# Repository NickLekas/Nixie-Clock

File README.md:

v1 is broken and required some bodge wires to work. I have not updated the schematic and PCB to correct my mistakes. It also has some deficencies in the dimming circuit resulint in a quiet, but audible whine.

v2 is in progress and will fix many issues and make the clock easier to update. It wil be using an RP2040.

Features
- Automatic time seting using GPS
- User sets their time zone using dip switches
- Tubes dim with ambient light
- Day light savings time will be controlled using a +/-1 switch 
- Plenty of test points for testing and hacking
- USB C for power and data

The goal of this is to be a program once project so the end user will never need to plug it into a computer. But if they do, the RP2040 will make firmware updates easy

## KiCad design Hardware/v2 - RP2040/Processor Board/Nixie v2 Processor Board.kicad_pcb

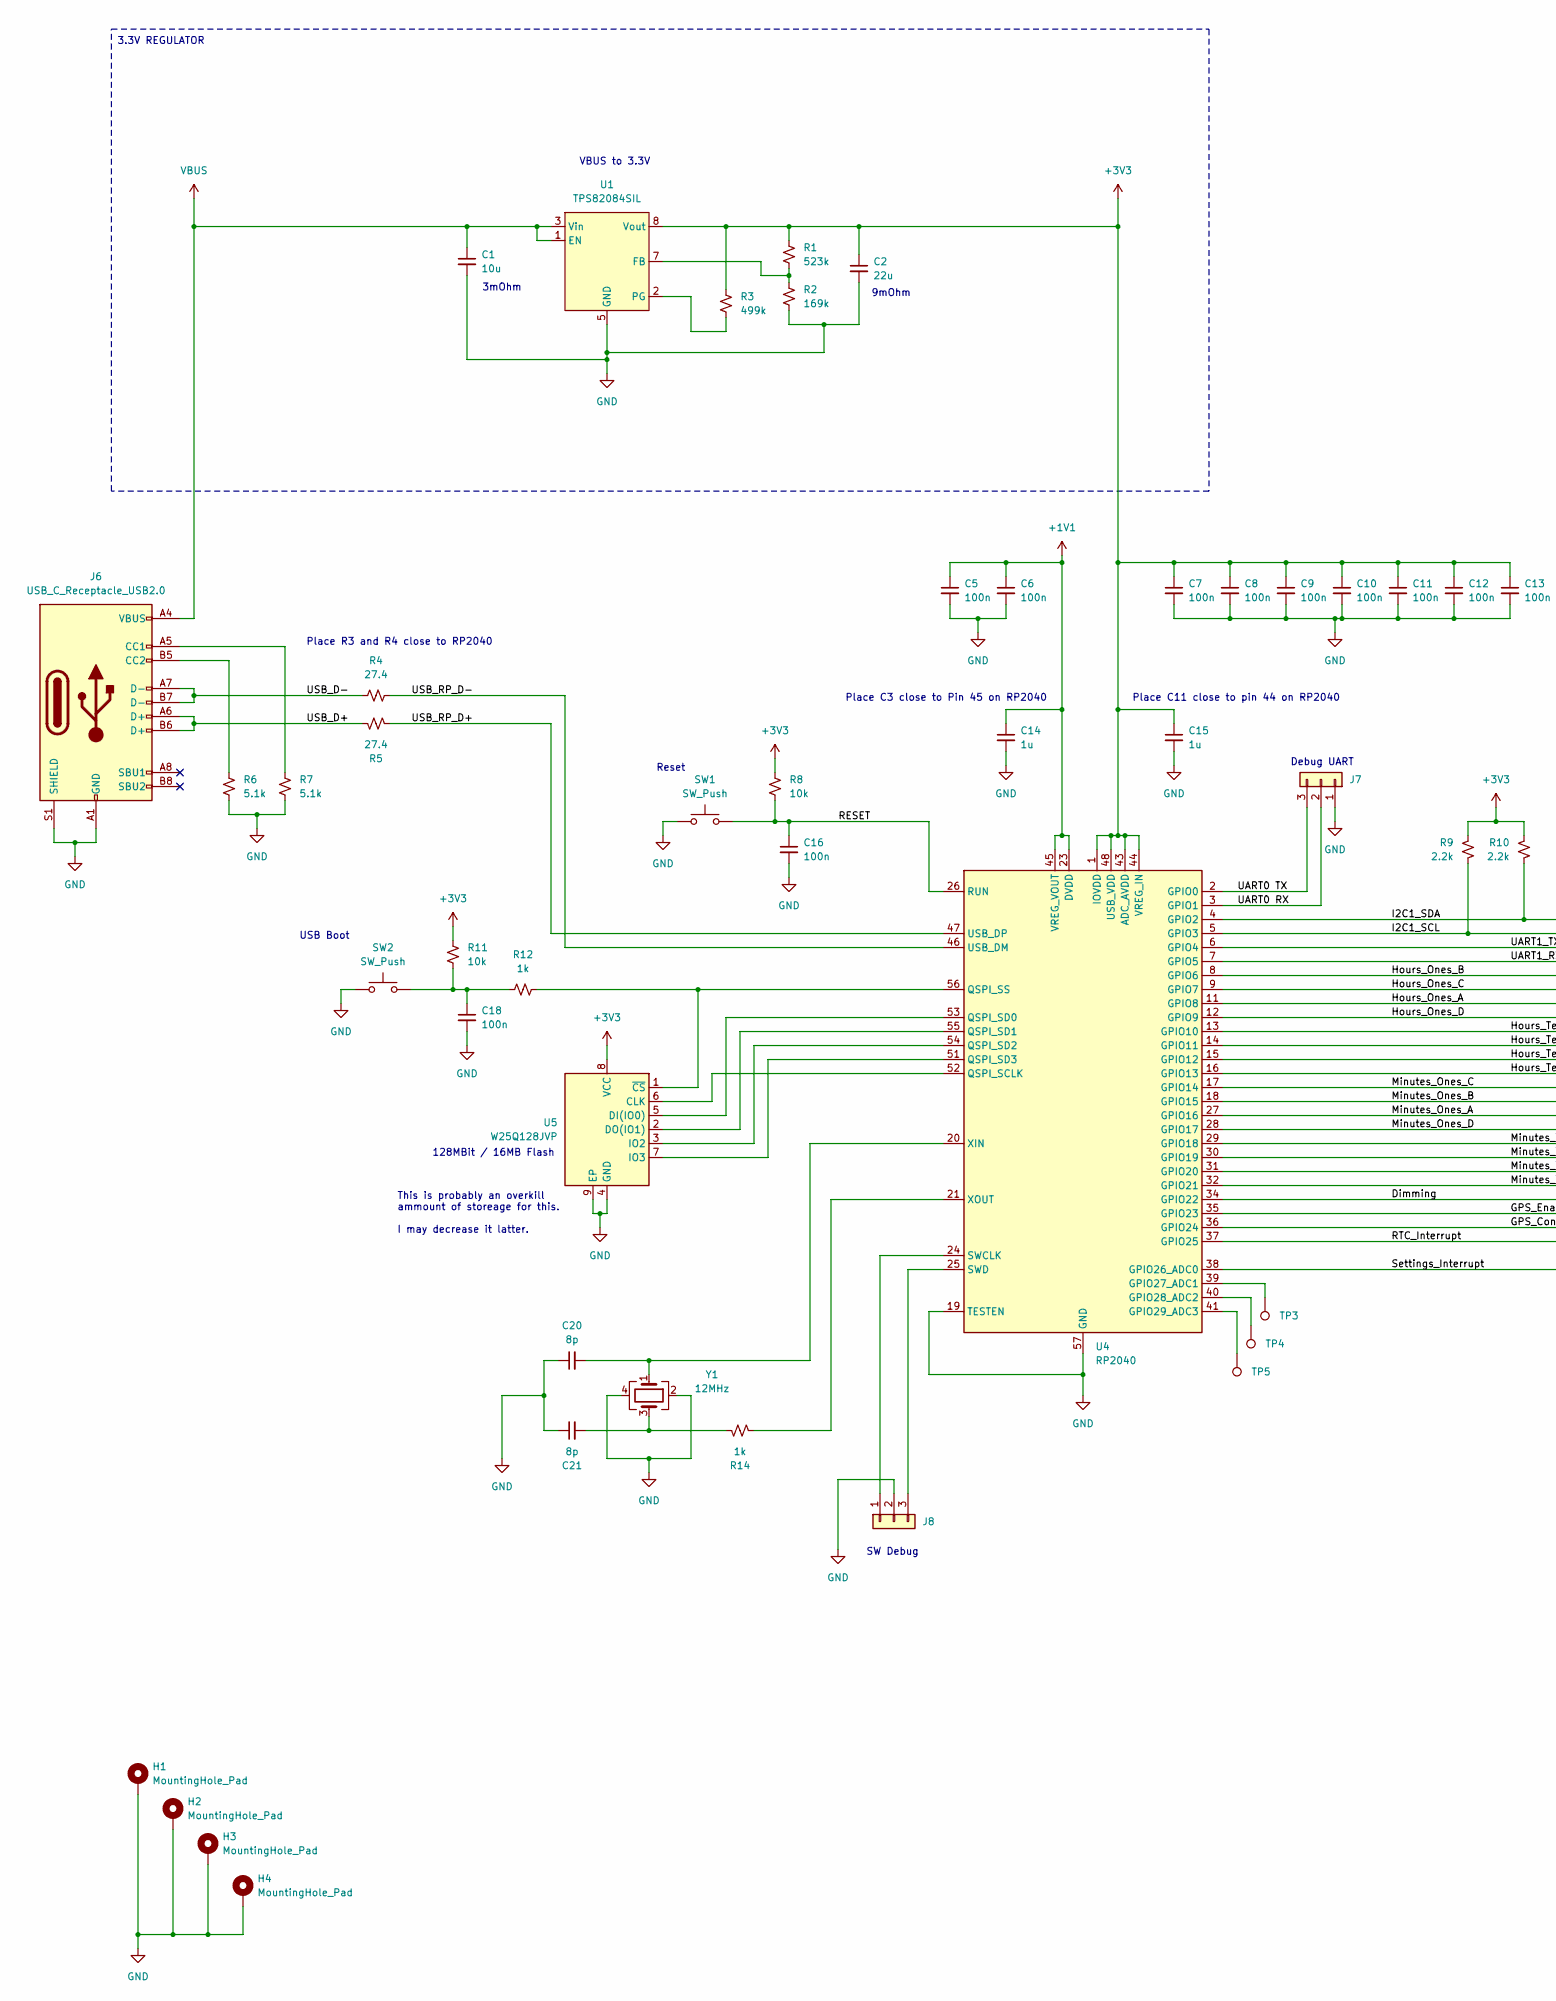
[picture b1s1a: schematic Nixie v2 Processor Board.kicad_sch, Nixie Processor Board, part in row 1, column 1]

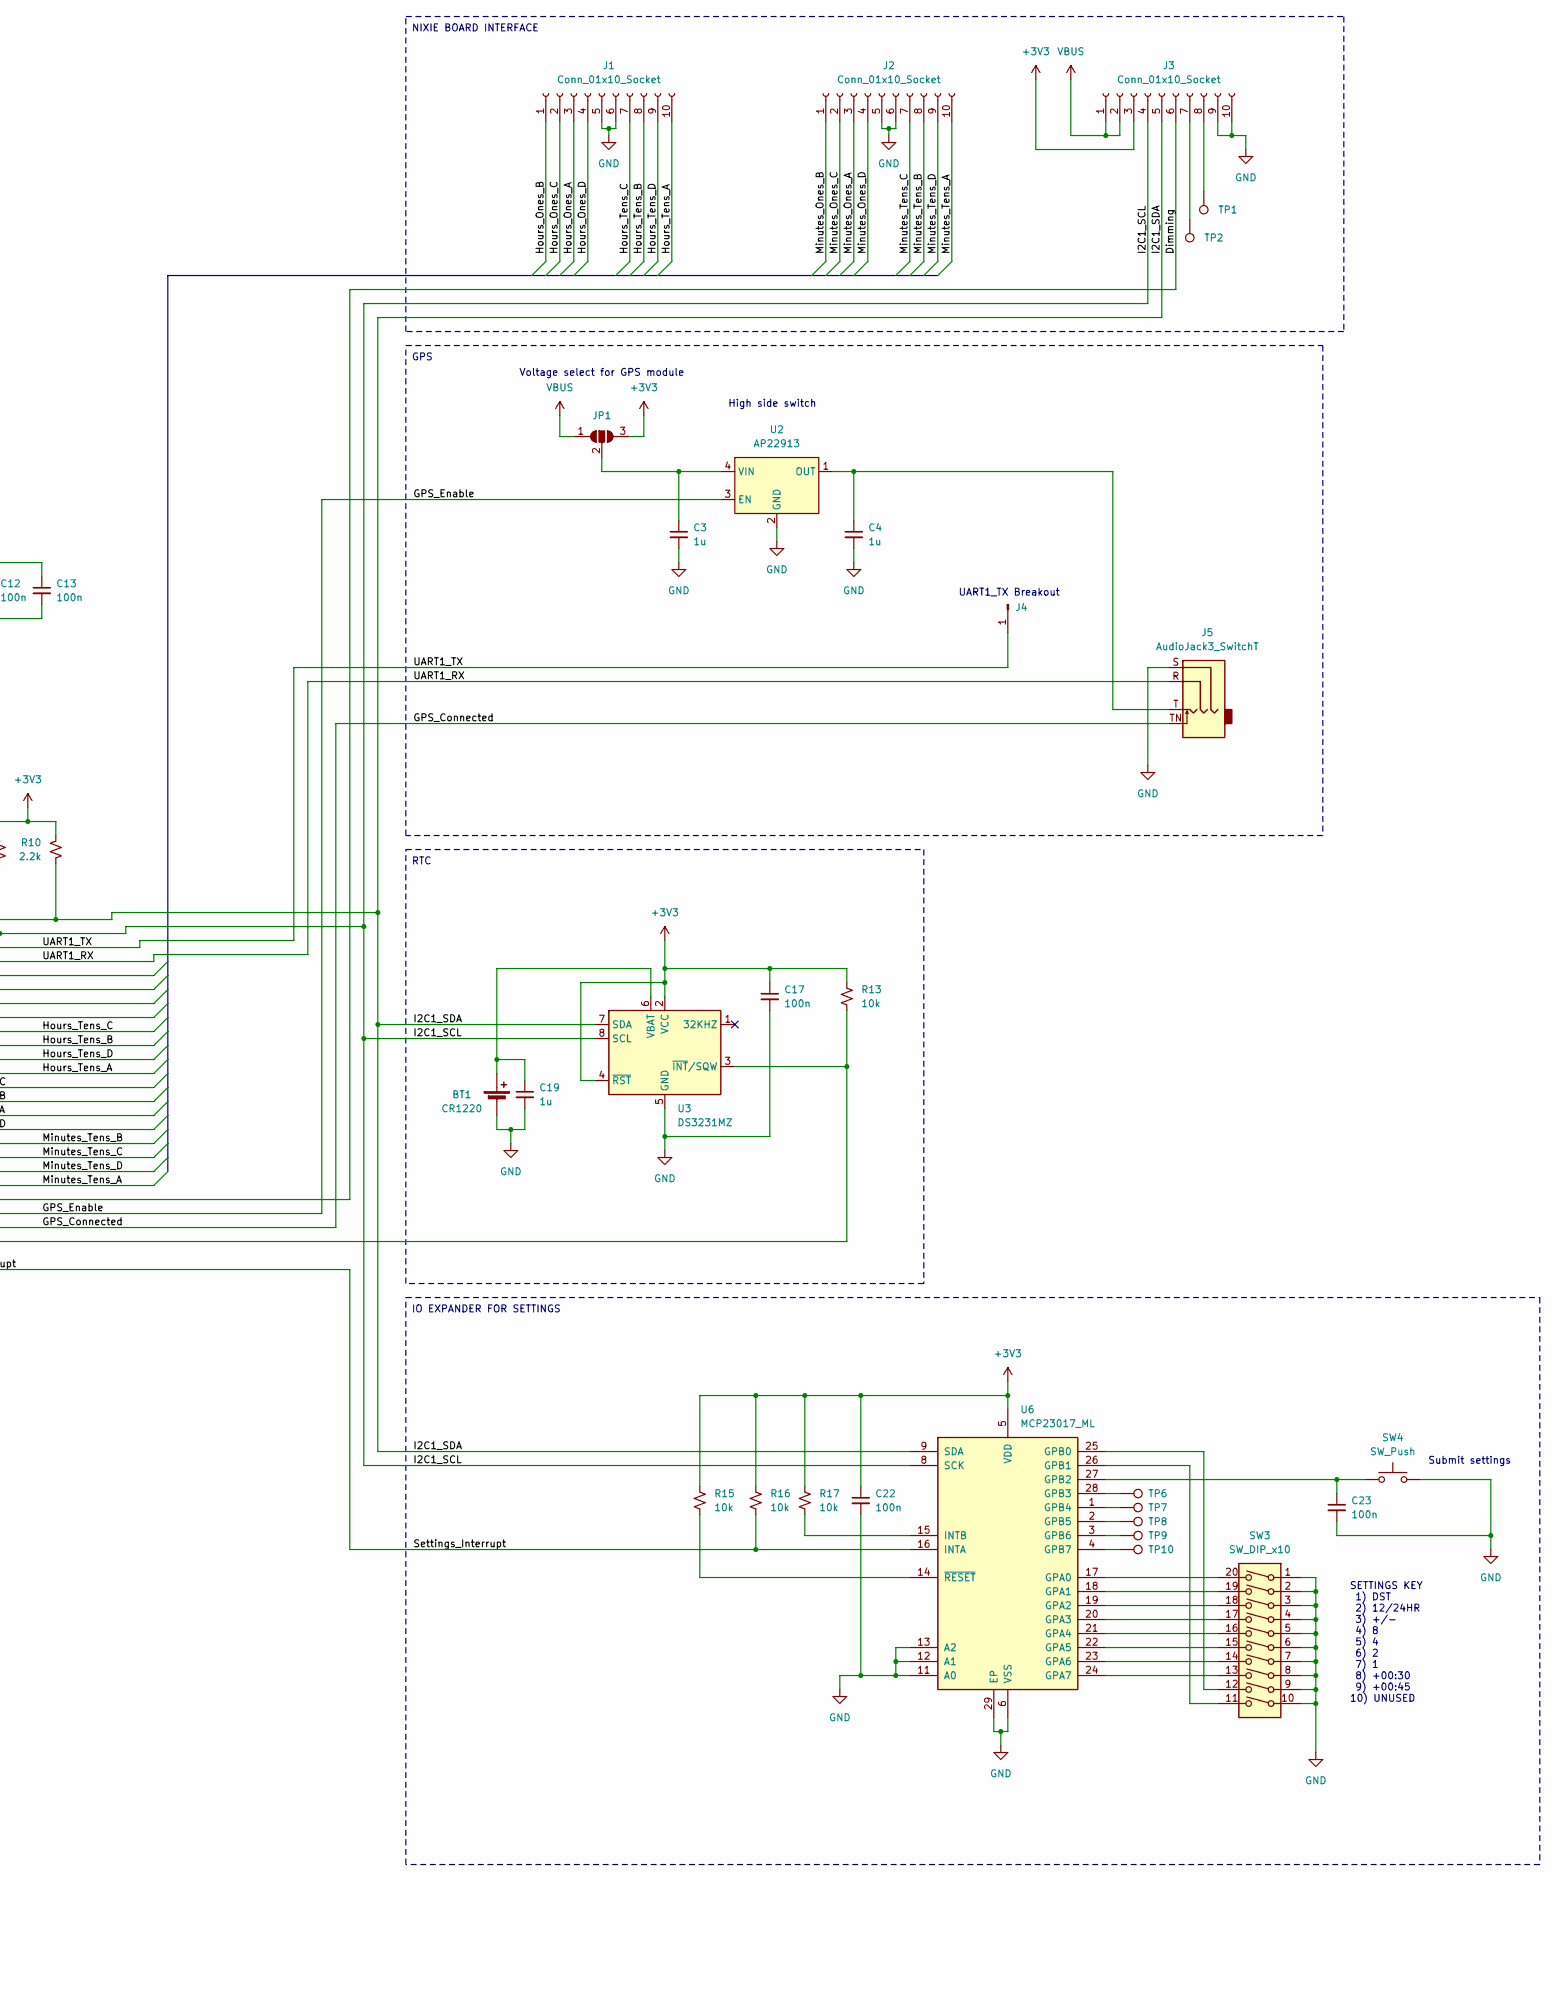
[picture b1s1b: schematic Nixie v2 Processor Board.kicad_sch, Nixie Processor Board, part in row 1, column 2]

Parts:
BT1: CR1220; BatteryHolder_LINX_BAT-HLD-012-SMT; MPN BK-916-TR
C1: 10u; C_0603_1608Metric
C2: 22u; C_0603_1608Metric
C3, C4, C19: 1u; C_0603_1608Metric
C5, C6, C7, C8, C9, C10, C11, C12, C13: 100n; C_0402_1005Metric
C14, C15: 1u; C_0402_1005Metric
C16, C17, C18, C22, C23: 100n; C_0603_1608Metric
C20, C21: 8p; C_0402_1005Metric
H1, H2, H3, H4: MountingHole_Pad; MountingHole_3.2mm_M3_Pad_Via
J1, J2, J3: Conn_01x10_Socket; PinSocket_2x05_P2.54mm_Vertical
J4: Conn_01x01_Pin; PinHeader_1x01_P2.54mm_Vertical
J5: AudioJack3_SwitchT; Jack_3.5mm_CUI_SJ-3524-SMT_Horizontal
J6: USB_C_Receptacle_USB2.0; USB_C_Receptacle_HRO_TYPE-C-31-M-12
J7, J8: Conn_01x03_2.54mm; PinHeader_1x03_P2.54mm_Vertical
JP1: SolderJumper_3_Open; SolderJumper-3_P1.3mm_Open_RoundedPad1.0x1.5mm_NumberLabels
R1: 523k; R_0603_1608Metric
R2: 169k; R_0603_1608Metric
R3: 499k; R_0603_1608Metric
R4, R5: 27.4; R_0402_1005Metric
R6, R7: 5.1k; R_0603_1608Metric
R8, R11, R13, R15, R16, R17: 10k; R_0603_1608Metric
R9, R10: 2.2k; R_0603_1608Metric
R12: 1k; R_0603_1608Metric
R14: 1k; R_0402_1005Metric
SW1, SW2, SW4: SW_Push; SW_Push_1P1T_NO_CK_KMR2; MPN KMR213G LFG
SW3: SW_DIP_x10; SW_DIP_SPSTx10_Piano_10.8x26.96mm_W7.62mm_P2.54mm; MPN 219-10MST
TP1, TP2, TP3, TP4, TP5, TP6, TP7, TP8, TP9, TP10: TestPoint; TestPoint_Pad_D2.0mm
U1: TPS82084SIL; MicroSiP 1.33mm
U2: AP22913; SOT-23-6
U3: DS3231MZ; SOIC-8_3.9x4.9mm_P1.27mm
U4: RP2040; QFN-56-1EP_7x7mm_P0.4mm_EP3.2x3.2mm
U5: W25Q128JVP; WSON-8-1EP_6x5mm_P1.27mm_EP3.4x4.3mm
U6: MCP23017_ML; QFN-28-1EP_6x6mm_P0.65mm_EP4.25x4.25mm
Y1: 12MHz; Crystal_SMD_Abracon_ABM10-4Pin_2.5x2.0mm; MPN ABM10-166-12.000MHZ-T3

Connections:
+1V1: C5.1, C6.1, C14.1, U4.23 (DVDD), U4.45 (VREG_VOUT), U4.50 (DVDD)
+3V3: C2.1, C7.1, C8.1, C9.1, C10.1, C11.1, C12.1, C13.1, C15.1, C17.1, C22.1, J3.3, JP1.3 (B), R1.2, R3.2, R8.2, R9.1, R10.1, R11.2, R13.1, R15.1, R16.1, R17.1, U1.8 (Vout), U3.2 (VCC), U3.4 (~RST), U4.1 (IOVDD), U4.10 (IOVDD), U4.22 (IOVDD), U4.33 (IOVDD), U4.42 (IOVDD), U4.43 (ADC_AVDD), U4.44 (VREG_IN), U4.48 (USB_VDD), U4.49 (IOVDD), U5.8 (VCC), U6.5 (VDD)
/Dimming: J3.6, U4.34 (GPIO22)
/GPS_Connected: J5.TN, U4.36 (GPIO24)
/GPS_Enable: U2.3 (EN), U4.35 (GPIO23)
/Hours_Ones_A: J1.3, U4.11 (GPIO8)
/Hours_Ones_B: J1.1, U4.8 (GPIO6)
/Hours_Ones_C: J1.2, U4.9 (GPIO7)
/Hours_Ones_D: J1.4, U4.12 (GPIO9)
/Hours_Tens_A: J1.10, U4.16 (GPIO13)
/Hours_Tens_B: J1.8, U4.14 (GPIO11)
/Hours_Tens_C: J1.7, U4.13 (GPIO10)
/Hours_Tens_D: J1.9, U4.15 (GPIO12)
/I2C1_SCL: J3.4, R9.2, U3.8 (SCL), U4.5 (GPIO3), U6.8 (SCK)
/I2C1_SDA: J3.5, R10.2, U3.7 (SDA), U4.4 (GPIO2), U6.9 (SDA)
/Minutes_Ones_A: J2.3, U4.27 (GPIO16)
/Minutes_Ones_B: J2.1, U4.18 (GPIO15)
/Minutes_Ones_C: J2.2, U4.17 (GPIO14)
/Minutes_Ones_D: J2.4, U4.28 (GPIO17)
/Minutes_Tens_A: J2.10, U4.32 (GPIO21)
/Minutes_Tens_B: J2.8, U4.29 (GPIO18)
/Minutes_Tens_C: J2.7, U4.30 (GPIO19)
/Minutes_Tens_D: J2.9, U4.31 (GPIO20)
/RESET: C16.1, R8.1, SW1.2, U4.26 (RUN)
/RTC_Interrupt: R13.2, U3.3 (~INT/SQW), U4.37 (GPIO25)
/Settings_Interrupt: R16.2, U4.38 (GPIO26_ADC0), U6.16 (INTA)
/UART0 RX: J7.2, U4.3 (GPIO1)
/UART0 TX: J7.3, U4.2 (GPIO0)
/UART1_RX: J5.R, U4.7 (GPIO5)
/UART1_TX: J4.1, U4.6 (GPIO4)
/USB_D+: J6.A6 (D+), J6.B6 (D+), R5.2
/USB_D-: J6.A7 (D-), J6.B7 (D-), R4.2
/USB_RP_D+: R5.1, U4.47 (USB_DP)
/USB_RP_D-: R4.1, U4.46 (USB_DM)
GND: BT1.2 (-), C1.2, C2.2, C3.2, C4.2, C5.2, C6.2, C7.2, C8.2, C9.2, C10.2, C11.2, C12.2, C13.2, C14.2, C15.2, C16.2, C17.2, C18.2, C19.2, C20.1, C21.1, C22.2, C23.2, H1.1, H2.1, H3.1, H4.1, J1.5, J1.6, J2.5, J2.6, J3.9, J3.10, J5.S, J6.A1 (GND), J6.A12 (GND), J6.B1 (GND), J6.B12 (GND), J6.S1 (SHIELD), J7.1, J8.2, R2.1, R6.1, R7.1, SW1.1, SW2.1, SW3.1, SW3.2, SW3.3, SW3.4, SW3.5, SW3.6, SW3.7, SW3.8, SW3.9, SW3.10, SW4.2, U1.5 (GND), U1.6 (GND), U1.9 (GND), U2.2 (GND), U2.5 (GND), U3.5 (GND), U4.19 (TESTEN), U4.57 (GND), U5.4 (GND), U5.9 (EP), U6.6 (VSS), U6.11 (A0), U6.12 (A1), U6.13 (A2), U6.29 (EP), Y1.2, Y1.4
unnamed: BT1.1 (+), C19.1, U3.6 (VBAT)
unnamed: C18.1, R11.1, R12.2, SW2.2
unnamed: C21.2, R14.2, Y1.3
unnamed: J3.7, TP2.1
unnamed: J3.8, TP1.1
unnamed: J6.A5 (CC1), R7.2
unnamed: J6.B5 (CC2), R6.2
unnamed: J8.1, U4.24 (SWCLK)
unnamed: J8.3, U4.25 (SWD)
unnamed: C3.1, JP1.2 (C), U2.4 (VIN), U2.6 (VIN)
unnamed: R1.1, R2.2, U1.7 (FB)
unnamed: R3.1, U1.2 (PG)
unnamed: C4.1, J5.T, U2.1 (OUT)
unnamed: TP3.1, U4.39 (GPIO27_ADC1)
unnamed: TP4.1, U4.40 (GPIO28_ADC2)
unnamed: TP5.1, U4.41 (GPIO29_ADC3)
unnamed: U4.52 (QSPI_SCLK), U5.6 (CLK)
unnamed: U4.53 (QSPI_SD0), U5.5 (DI(IO0))
unnamed: U4.55 (QSPI_SD1), U5.2 (DO(IO1))
unnamed: U4.54 (QSPI_SD2), U5.3 (IO2)
unnamed: U4.51 (QSPI_SD3), U5.7 (IO3)
unnamed: R12.1, U4.56 (QSPI_SS), U5.1 (~CS)
unnamed: C20.2, U4.20 (XIN), Y1.1
unnamed: R14.1, U4.21 (XOUT)
unnamed: SW3.20, U6.17 (GPA0)
unnamed: SW3.19, U6.18 (GPA1)
unnamed: SW3.18, U6.19 (GPA2)
unnamed: SW3.17, U6.20 (GPA3)
unnamed: SW3.16, U6.21 (GPA4)
unnamed: SW3.15, U6.22 (GPA5)
unnamed: SW3.14, U6.23 (GPA6)
unnamed: SW3.13, U6.24 (GPA7)
unnamed: SW3.12, U6.25 (GPB0)
unnamed: SW3.11, U6.26 (GPB1)
unnamed: C23.1, SW4.1, U6.27 (GPB2)
unnamed: TP6.1, U6.28 (GPB3)
unnamed: TP7.1, U6.1 (GPB4)
unnamed: TP8.1, U6.2 (GPB5)
unnamed: TP9.1, U6.3 (GPB6)
unnamed: TP10.1, U6.4 (GPB7)
unnamed: R17.2, U6.15 (INTB)
unnamed: R15.2, U6.14 (~RESET)
VBUS: C1.1, J3.1, J3.2, J6.A4 (VBUS), J6.A9 (VBUS), J6.B4 (VBUS), J6.B9 (VBUS), JP1.1 (A), U1.1 (EN), U1.3 (Vin), U1.4 (Vin)

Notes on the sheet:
SW Debug
Place C11 close to pin 44 on RP2040
9mOhm
This is probably an overkill ammount of storeage for this. I may decrease it latter.
RTC
3mOhm
Voltage select for GPS module
GPS
Debug UART
Submit settings
High side switch
USB Boot
Place C3 close to Pin 45 on RP2040
Place R3 and R4 close to RP2040
128MBit / 16MB Flash
NIXIE BOARD INTERFACE
UART1_TX Breakout
3.3V REGULATOR
SETTINGS KEY 1) DST 2) 12/24HR 3) +/- 4) 8 5) 4 6) 2 7) 1 8) +00:30 9) +00:45 10) UNUSED
VBUS to 3.3V
IO EXPANDER FOR SETTINGS
Reset

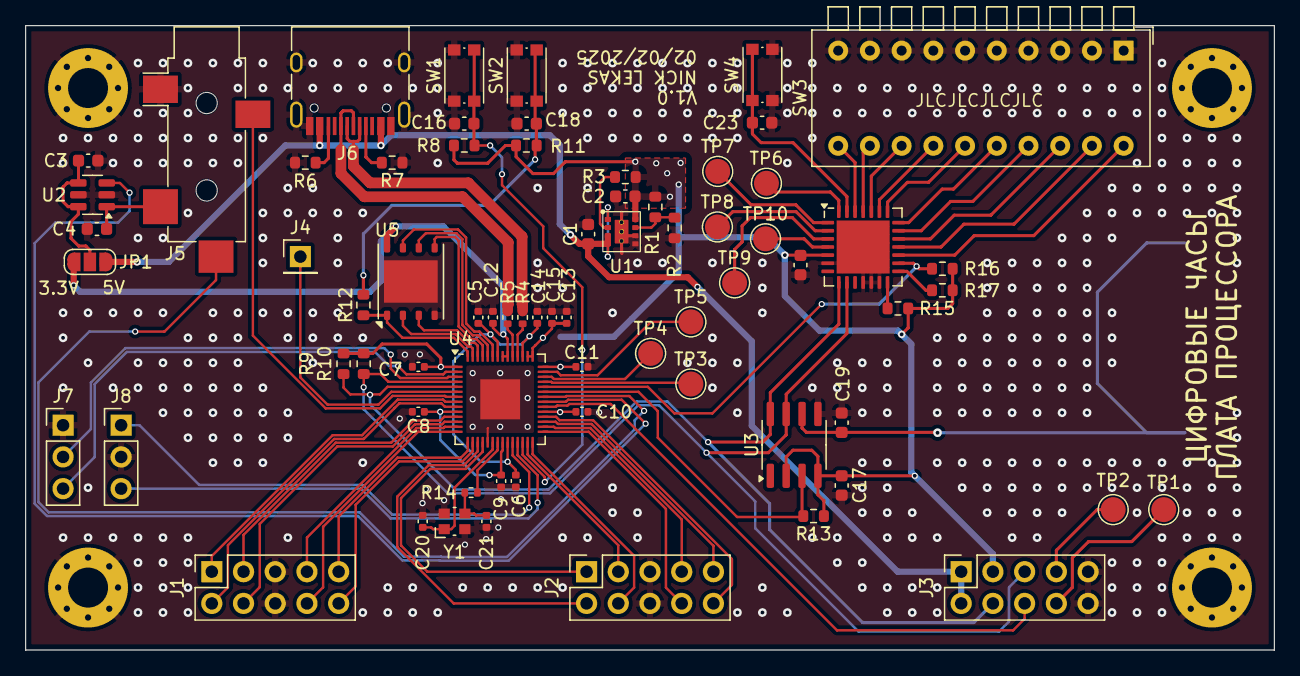
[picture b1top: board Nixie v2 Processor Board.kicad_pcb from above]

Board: 2 copper layers, 100.0 x 50.0 mm, 75 parts (1 on the bottom side), 78 nets.

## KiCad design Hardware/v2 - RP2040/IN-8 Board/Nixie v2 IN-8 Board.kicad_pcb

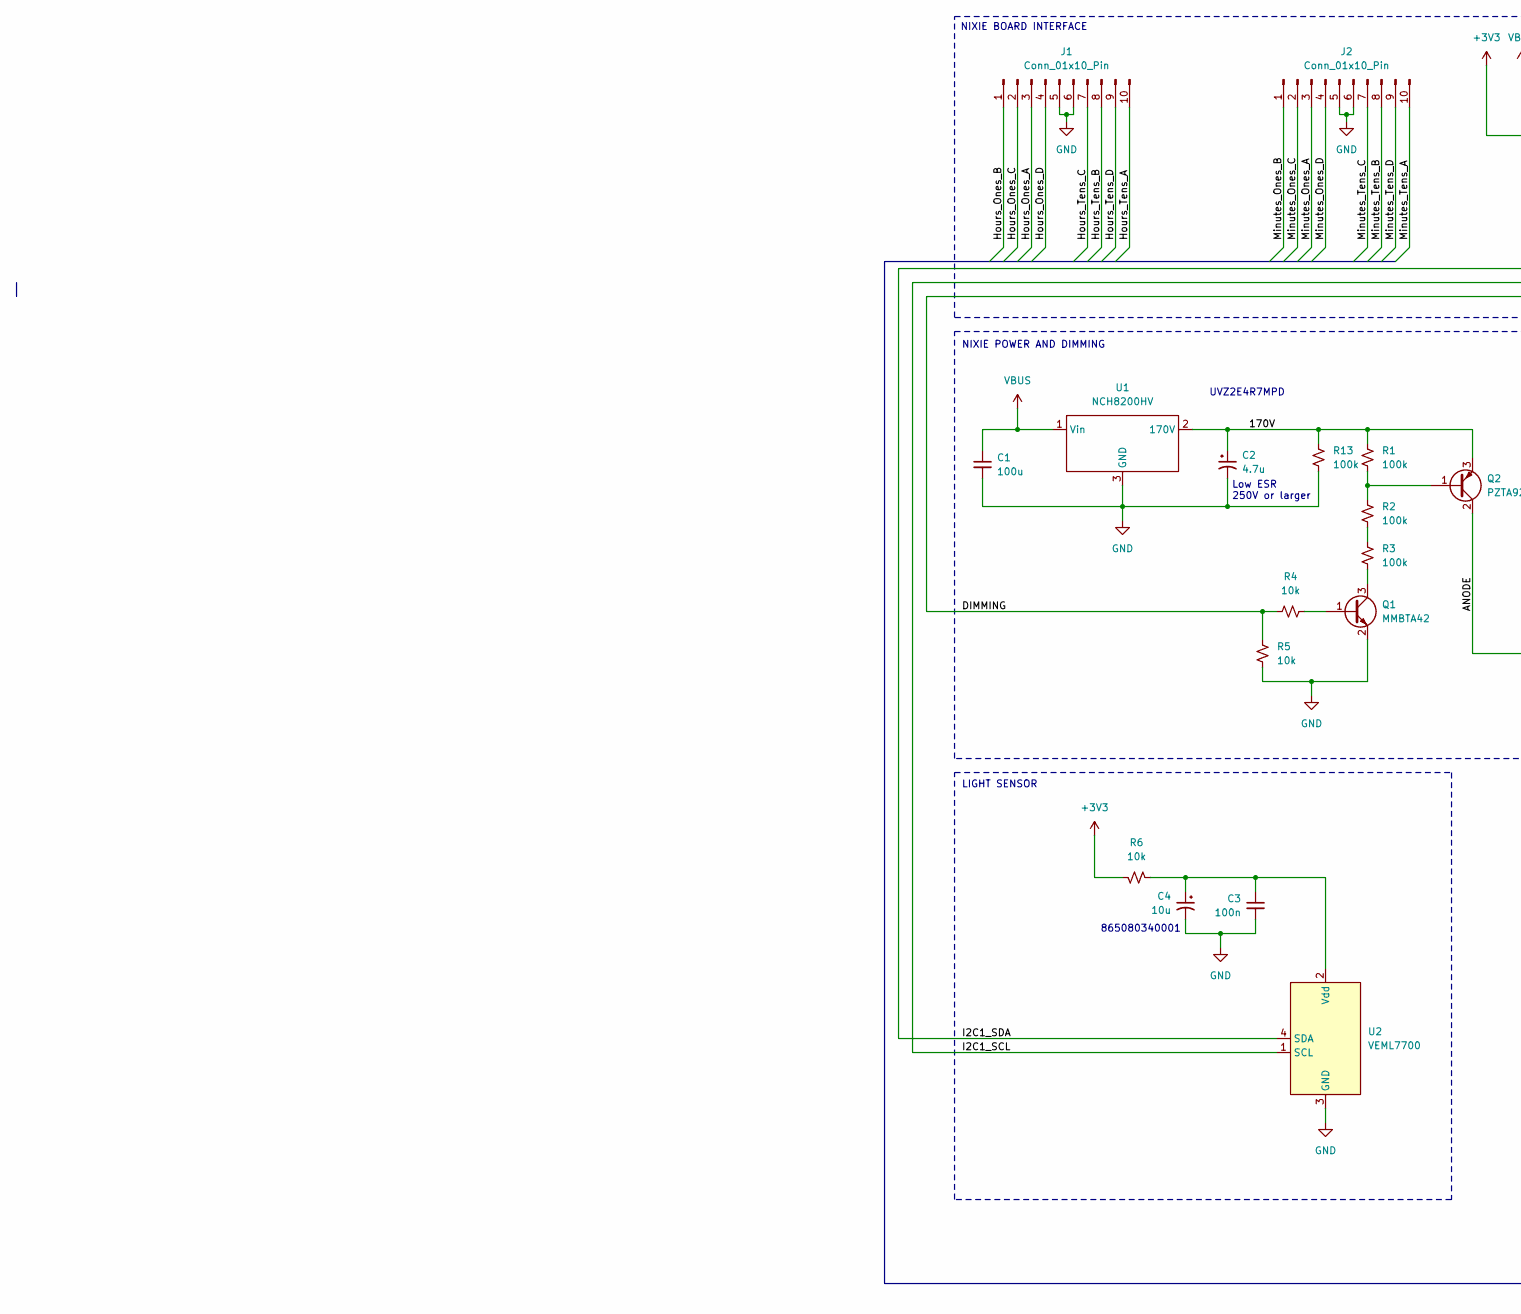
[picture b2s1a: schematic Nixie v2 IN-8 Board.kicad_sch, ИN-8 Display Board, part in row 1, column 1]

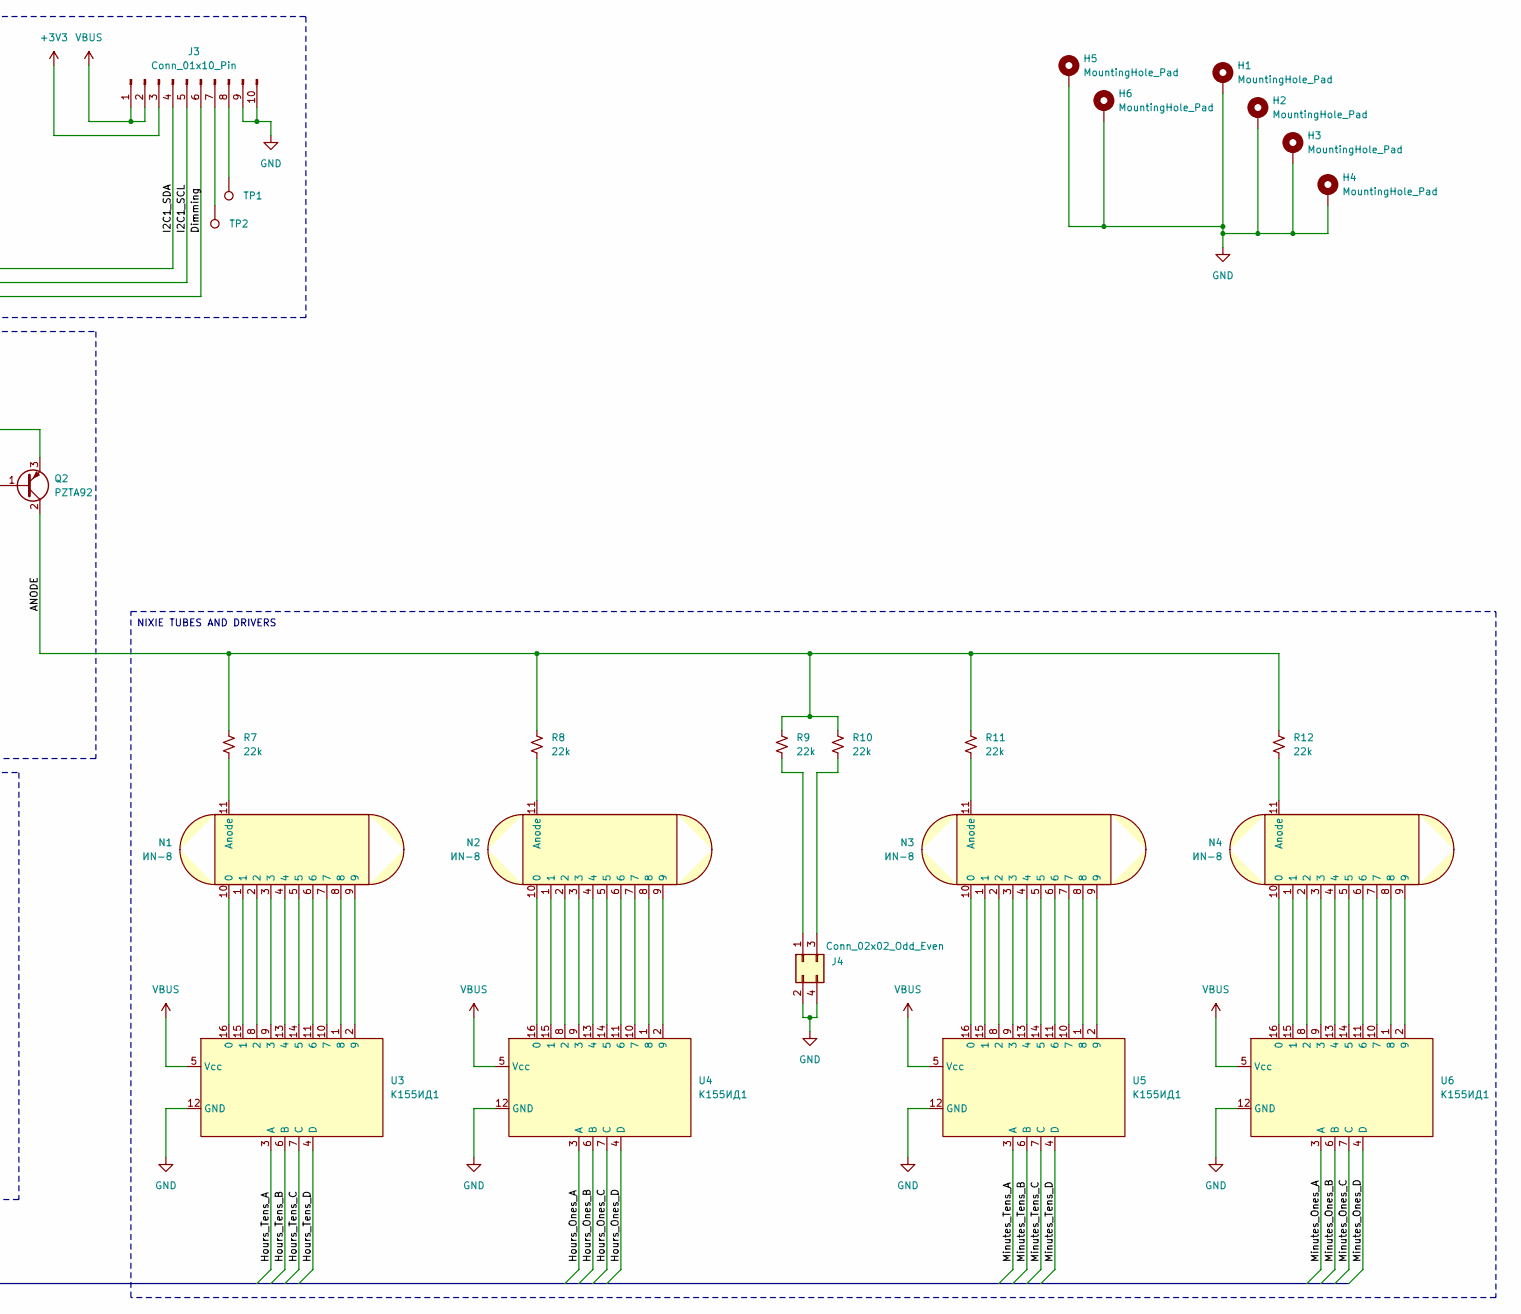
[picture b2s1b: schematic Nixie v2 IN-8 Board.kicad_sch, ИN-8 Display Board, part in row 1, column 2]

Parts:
C1: 100u; C_0603_1608Metric
C2: 4.7u; CP_Radial_D8.0mm_P3.50mm
C3: 100n; C_0603_1608Metric
C4: 10u; CP_Elec_4x5.4
H1, H2, H3, H4, H5, H6: MountingHole_Pad; MountingHole_3.2mm_M3_Pad_Via
J1, J2, J3: Conn_01x10_Pin; PinHeader_2x05_P2.54mm_Vertical
J4: Conn_02x02_Odd_Even; PinSocket_2x02_P2.54mm_Vertical
N1, N2, N3, N4: ИN-8
Q1: MMBTA42; SOT-23
Q2: PZTA92; SOT-223-3_TabPin2
R1, R2, R3: 100k; R_0603_1608Metric
R4, R5, R6: 10k; R_0603_1608Metric
R7, R8, R9, R10, R11, R12: 22k; R_0805_2012Metric
R13: 100k; R_0805_2012Metric
TP1, TP2: TestPoint; TestPoint_Pad_D2.0mm
U1: NCH8200HV
U2: VEML7700; VEML7700-TV
U3, U4, U5, U6: К155ИД1; DIP-16_W7.62mm

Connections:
+3V3: J3.3, R6.2
/170V: C2.1, Q2.3 (E), R1.1, R13.1, U1.2 (170V)
/ANODE: Q2.2 (C), R7.1, R8.1, R9.1, R10.1, R11.1, R12.1
/DIMMING: J3.6, R4.1, R5.1
/Hours_Ones_A: J1.3, U4.3 (A)
/Hours_Ones_B: J1.1, U4.6 (B)
/Hours_Ones_C: J1.2, U4.7 (C)
/Hours_Ones_D: J1.4, U4.4 (D)
/Hours_Tens_A: J1.10, U3.3 (A)
/Hours_Tens_B: J1.8, U3.6 (B)
/Hours_Tens_C: J1.7, U3.7 (C)
/Hours_Tens_D: J1.9, U3.4 (D)
/I2C1_SCL: J3.5, U2.1 (SCL)
/I2C1_SDA: J3.4, U2.4 (SDA)
/Minutes_Ones_A: J2.3, U6.3 (A)
/Minutes_Ones_B: J2.1, U6.6 (B)
/Minutes_Ones_C: J2.2, U6.7 (C)
/Minutes_Ones_D: J2.4, U6.4 (D)
/Minutes_Tens_A: J2.10, U5.3 (A)
/Minutes_Tens_B: J2.8, U5.6 (B)
/Minutes_Tens_C: J2.7, U5.7 (C)
/Minutes_Tens_D: J2.9, U5.4 (D)
GND: C1.2, C2.2, C3.2, C4.2, H1.1, H2.1, H3.1, H4.1, H5.1, H6.1, J1.5, J1.6, J2.5, J2.6, J3.9, J3.10, J4.2, J4.4, Q1.2 (E), R5.2, R13.2, U1.3 (GND), U1.4 (GND), U2.3 (GND), U3.12 (GND), U4.12 (GND), U5.12 (GND), U6.12 (GND)
unnamed: J3.7, TP2.1
unnamed: J3.8, TP1.1
unnamed: J4.1, R9.2
unnamed: J4.3, R10.2
unnamed: N1.10 (0), U3.16 (0)
unnamed: N1.11 (Anode), R7.2
unnamed: N2.10 (0), U4.16 (0)
unnamed: N2.11 (Anode), R8.2
unnamed: N3.10 (0), U5.16 (0)
unnamed: N3.11 (Anode), R11.2
unnamed: N4.10 (0), U6.16 (0)
unnamed: N4.11 (Anode), R12.2
unnamed: Q1.1 (B), R4.2
unnamed: Q1.3 (C), R3.2
unnamed: Q2.1 (B), R1.2, R2.1
unnamed: R2.2, R3.1
unnamed: C3.1, C4.1, R6.1, U2.2 (Vdd)
unnamed: N1.1, U3.15 (1)
unnamed: N1.2, U3.8 (2)
unnamed: N1.3, U3.9 (3)
unnamed: N1.4, U3.13 (4)
unnamed: N1.5, U3.14 (5)
unnamed: N1.6, U3.11 (6)
unnamed: N1.7, U3.10 (7)
unnamed: N1.8, U3.1 (8)
unnamed: N1.9, U3.2 (9)
unnamed: N2.1, U4.15 (1)
unnamed: N2.2, U4.8 (2)
unnamed: N2.3, U4.9 (3)
unnamed: N2.4, U4.13 (4)
unnamed: N2.5, U4.14 (5)
unnamed: N2.6, U4.11 (6)
unnamed: N2.7, U4.10 (7)
unnamed: N2.8, U4.1 (8)
unnamed: N2.9, U4.2 (9)
unnamed: N3.1, U5.15 (1)
unnamed: N3.2, U5.8 (2)
unnamed: N3.3, U5.9 (3)
unnamed: N3.4, U5.13 (4)
unnamed: N3.5, U5.14 (5)
unnamed: N3.6, U5.11 (6)
unnamed: N3.7, U5.10 (7)
unnamed: N3.8, U5.1 (8)
unnamed: N3.9, U5.2 (9)
unnamed: N4.1, U6.15 (1)
unnamed: N4.2, U6.8 (2)
unnamed: N4.3, U6.9 (3)
unnamed: N4.4, U6.13 (4)
unnamed: N4.5, U6.14 (5)
unnamed: N4.6, U6.11 (6)
unnamed: N4.7, U6.10 (7)
unnamed: N4.8, U6.1 (8)
unnamed: N4.9, U6.2 (9)
VBUS: C1.1, J3.1, J3.2, U1.1 (Vin), U3.5 (Vcc), U4.5 (Vcc), U5.5 (Vcc), U6.5 (Vcc)

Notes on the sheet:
NIXIE POWER AND DIMMING
LIGHT SENSOR
NIXIE BOARD INTERFACE
Low ESR 250V or larger
NIXIE TUBES AND DRIVERS
UVZ2E4R7MPD
865080340001

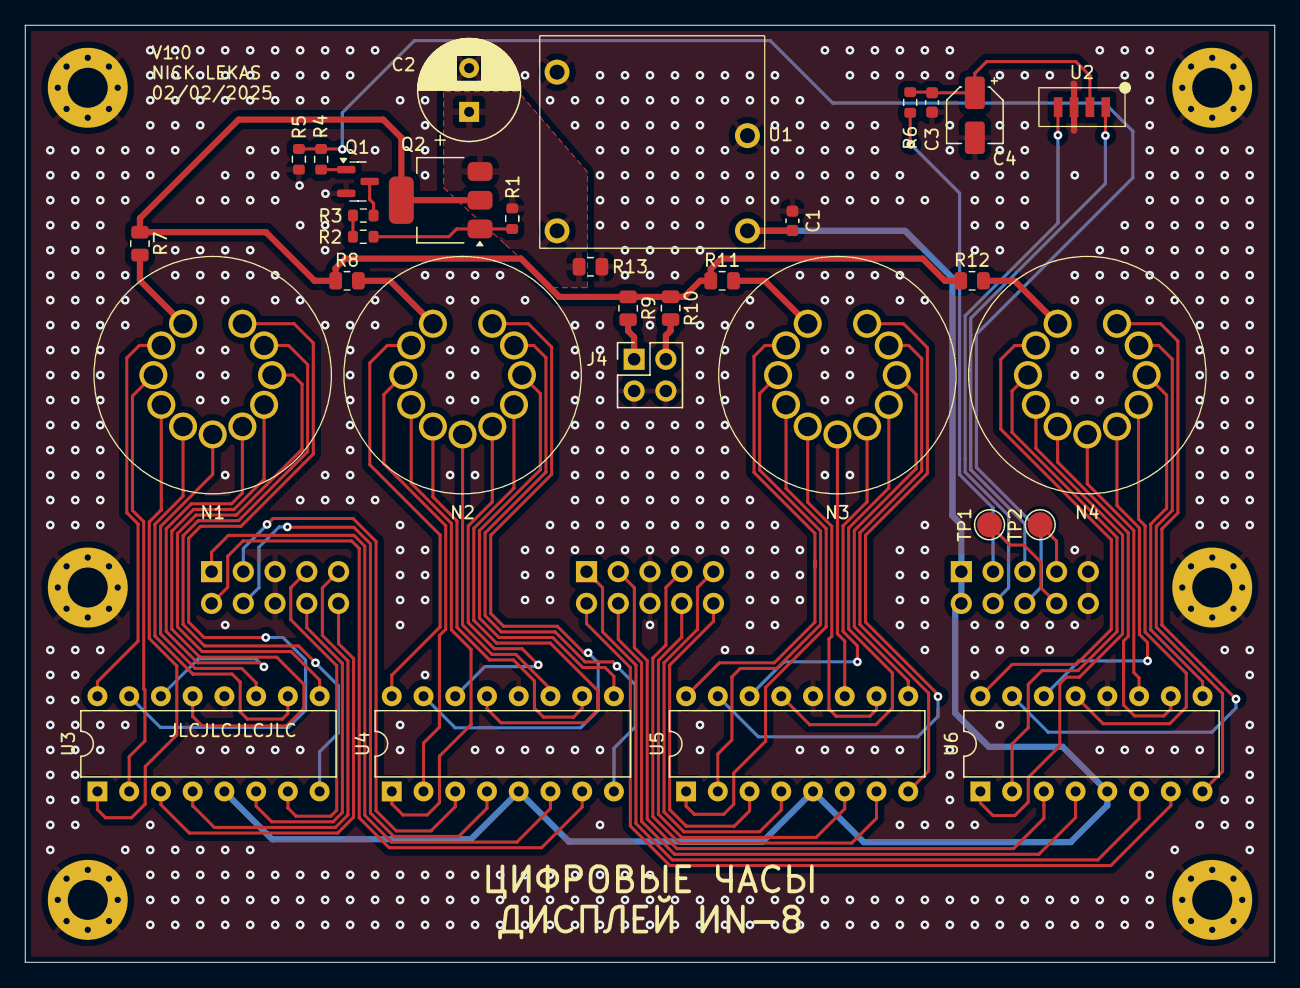
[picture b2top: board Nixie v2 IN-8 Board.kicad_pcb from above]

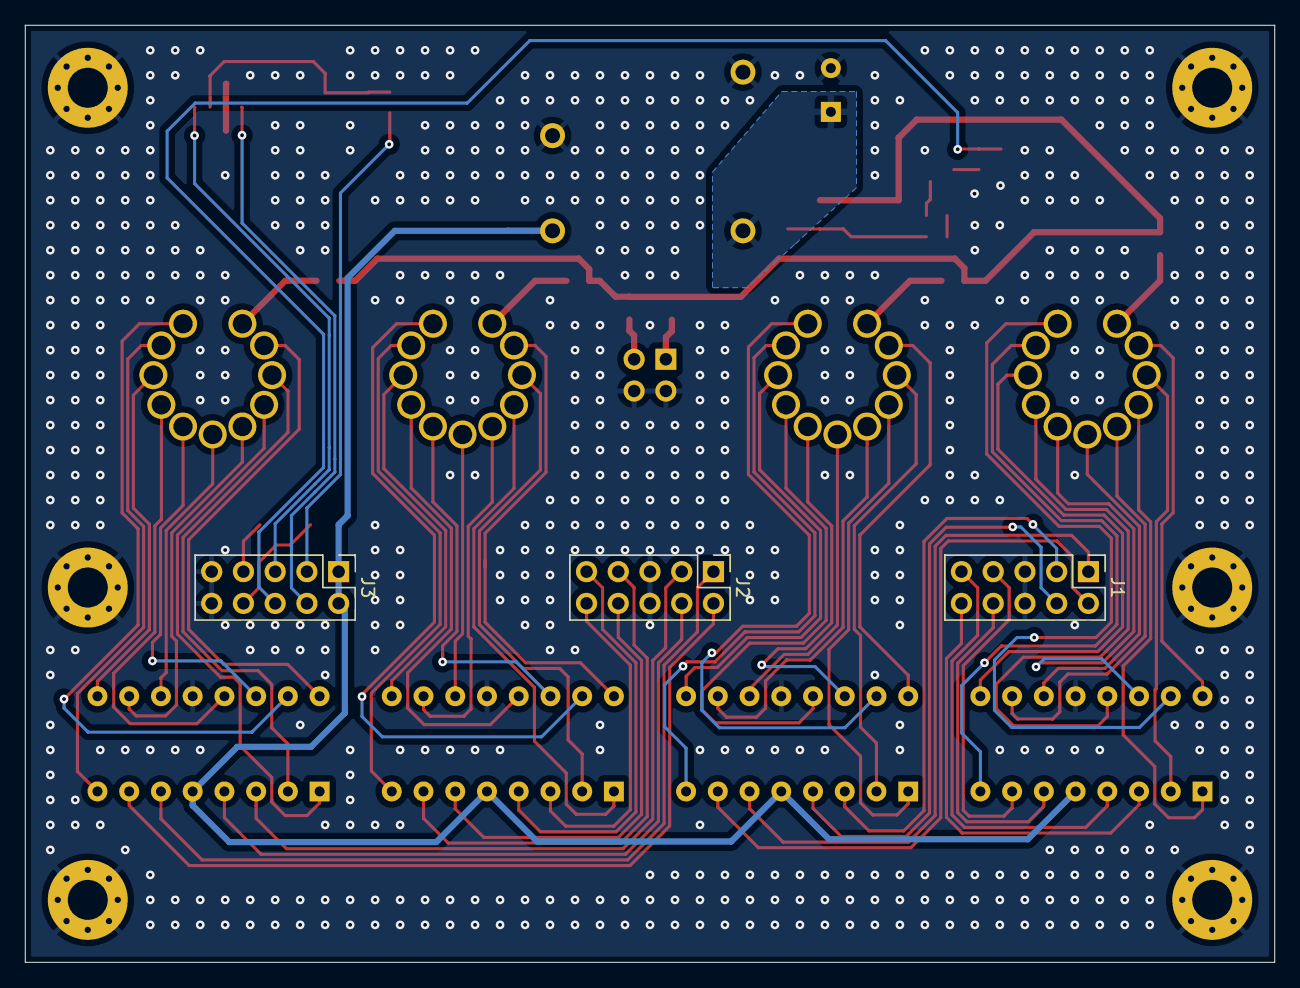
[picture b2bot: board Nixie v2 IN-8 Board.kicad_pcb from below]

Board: 2 copper layers, 100.0 x 75.0 mm, 41 parts (3 on the bottom side), 77 nets.
